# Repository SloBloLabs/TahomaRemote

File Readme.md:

# Tahoma Remote

## Overview
This device is an internet independent shutter control using the Tahoma Local API. At the same time, it serves as a proof of concept for integration of STM32F405 MCU with an ESP8266 using UART communication and Espressif AT command set.

Both hard and software are tailored to the requirements of my domestic Somfy roller shutter installation, consisting of 9 roller shutters controlled by a Tahoma Switch. The layout of buttons reflect the location of roller shutters looking top down to the flat for easy orientation. Adding/removing shutters to the setup is possible, but may require adaption of both hard and software.

This repository contains all ressources to build the device:
 * the firmware for the STM32 MCU
 * a script to upload ESP AT firmware to the ESP MCU
 * the board's KiCad design
 * a 3D model housing the board

## Operation
 * Switch the device on
 * During the startup sequence, Tahoma Remote
   * initializes communication to ESP
   * sets up WIFI connection
   * fetches current shutter states from Tahoma Switch
 * The button colours reflect the actual shutter closures of each motor in HSV colour space:
   * green = up
   * blue = 50%
   * red = closed
   * and any colour inbetween
 * Choose your target closure amount using the slider pot
 * Hit the buttons of corresponding shutters to execute the target closure command
 * While motors are moving, corresponding buttons are blinking
 * Motor status is updated each 1,5 seconds

## Highlights
As a proof of concept, these are the feature highlights of the project:
 * DMA driven UART communication between STM32F405 and ESP8266
 * Client side implementation of AT command set
 * Using Tahoma Local API. No internet required!
 * JSON stream parsing for memory efficient payload consumption (big up for the great [lwjson](https://github.com/MaJerle/lwjson.git) project!)
 * Highly capable RGB Led driver implementation using DMA, I2C and PCA9685PW driver chips
 * FreeRTOS for independent UI and communication threads
 * All firmware code written in plain C/C++ using STM32 LL (Low Level) API
 * Compact design
 * Battery powered

## Installation Notes
### Flashing ESP Firmware
 1. Install esptool using

        brew install esptool
 2. Go to https://github.com/espressif/esp-at/releases and find the link for the latest ESP8266 compatible AT firmware, such as

    [ESP-WROOM-02-AT-V2.3.0.0.zip](https://dl.espressif.com/esp-at/firmwares/esp8266/ESP-WROOM-02-AT-V2.3.0.0.zip)
 3. Download and extract the file into ESP subfolder.<br>
    Within the "factory" subfolder, the archive will contain the firmware binary file called "factory/factory_WROOM-02.bin"

 4. Connect a USB serial adapter such as FTDI Friend or Arduino Uno

        USB Serial Adapter            Tahoma Remote
                       GND ---------> GND
                        TX ---------> EDTX
                        RX ---------> EDRX

 5. Press and hold the ESP Boot button on Tahoma Remote and switch the device on. Then release the button again.
 6. Go to ESP subfolder and issue uploadATFW.sh script (check and apply correct settings regarding PORT and FWPATH variable!)

        ./uploadATFW.sh

    If the command is not executable, add respective rights to it:

        chmod u+x uploadATFW.sh
    
    The expected output looks something like this:

        esptool v5.1.0
        Connected to ESP8266 on /dev/cu.usbserial-XXX:
        Chip type:          ESP8266EX
        Features:           Wi-Fi, 160MHz
        Crystal frequency:  26MHz
        MAC:                e0:98:06:0a:71:a6
        
        Stub flasher running.
        
        Configuring flash size...
        Flash will be erased from 0x00000000 to 0x001fffff...
        Flash parameters set to 0x0241.
        Wrote 2097152 bytes (582385 compressed) at 0x00000000 in 54.0 seconds (310.8 kbit/s).
        Hash of data verified.
        
        Hard resetting via RTS pin...
    
### Flashing STM32 firmware
 1. Install VS Code
 2. Install STM32Cube Extensions for VS Code
 3. Add lwjson as submodule to the project

        git submodule add https://github.com/MaJerle/lwjson.git
        git submodule update --init
 4. Rename config_example.h to config.h and configure your local credentials and system information:
   * WIFI_SSID: your WIFI SSID
   * WIFI_PASSWD: your WIFI password
   * TAHOMA_HOST: the Tahoma Switch hostname, typically in the form 'gateway-\<box pin code\>.local'
   * TAHOMA_AUTH: the developer token generated within Somfy App
   * shutterConfigTable takes a set of roller shutters in the system (see TahomaManger.h for the structure of ShutterConfig entries)
 5. Configure and build the project using device STM32F405RGT6 and GCC toolchain in VSCode
    
    alternatively, if cmake and ninja are installed on the system, you can run these commands:

        cmake --preset Release
        cmake --build --preset Release
 6. Connect ST-Link to the SWO interface on Tahoma Remote
 7. Flash the firmware: Run and Debug and apply "STM32Cube: STLink GDB Server"

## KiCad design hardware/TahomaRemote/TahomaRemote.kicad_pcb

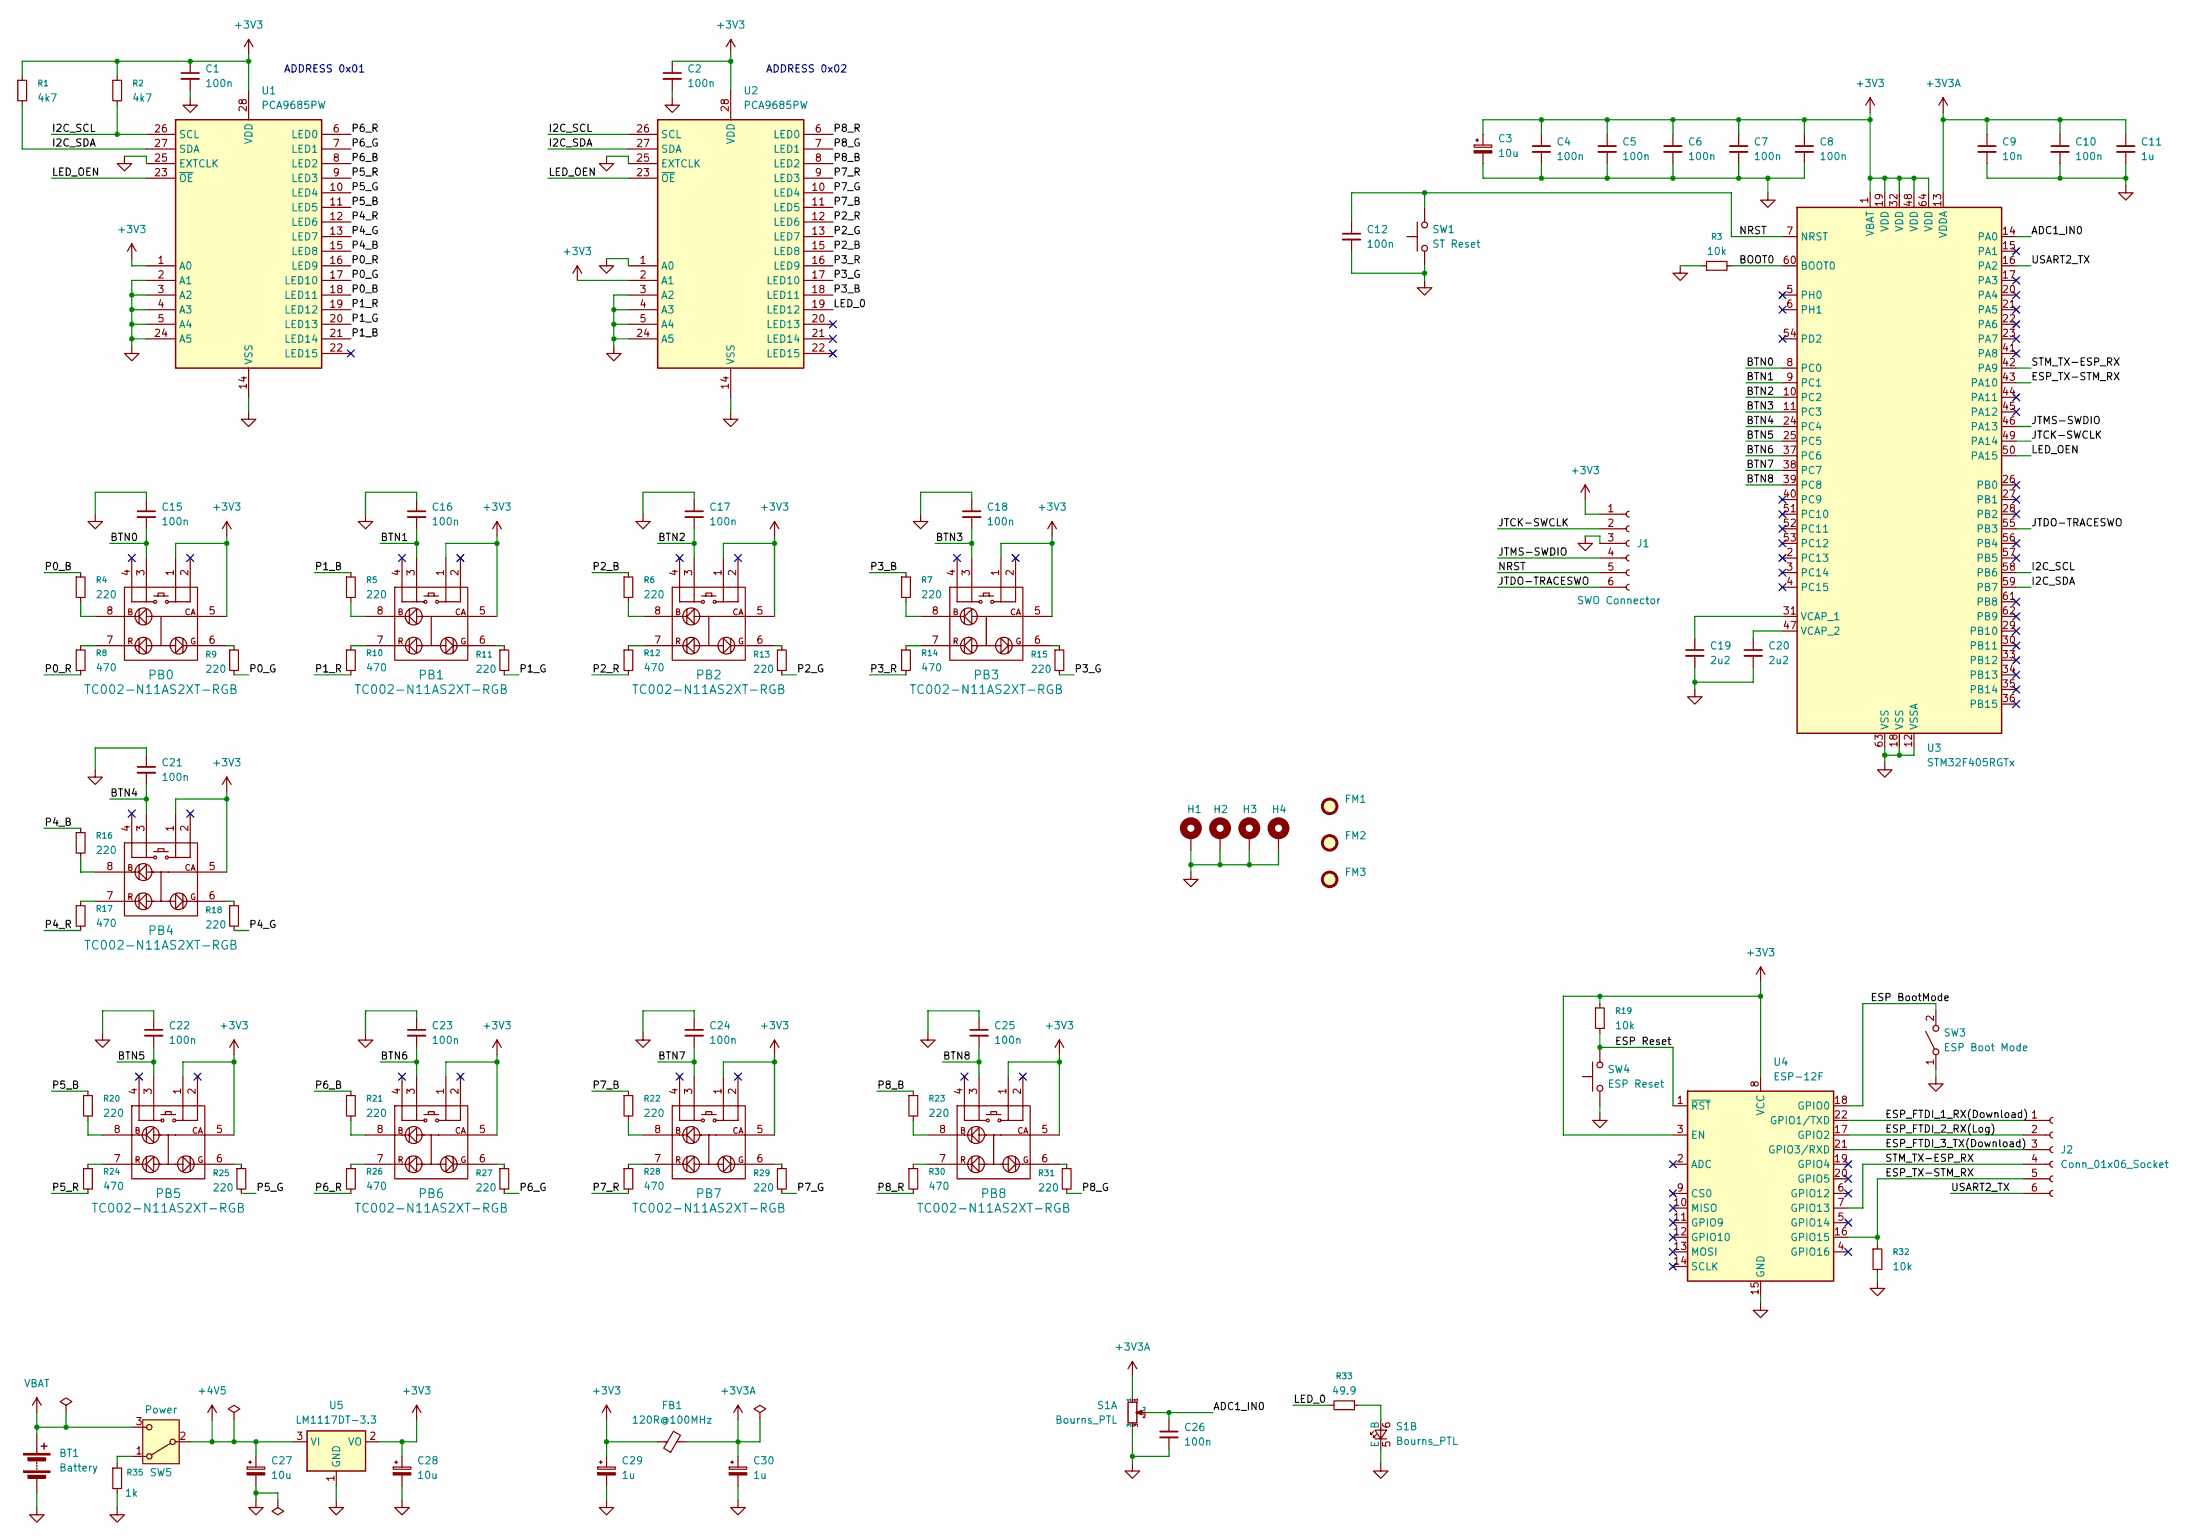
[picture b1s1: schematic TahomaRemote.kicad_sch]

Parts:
BT1: Battery; PinHeader_1x02_P2.54mm_Vertical
C1, C2, C4, C5, C6, C7, C8, C10, C12, C15, C16, C17, C18, C21, C22, C23, C24, C25, C26: 100n; C_0402_1005Metric; LCSC C1525
C3, C27, C28: 10u; CP_EIA-3216-18_Kemet-A; LCSC C7171
C9: 10n; C_0402_1005Metric; LCSC C15195
C11, C29, C30: 1u; C_0402_1005Metric; LCSC C52923
C19, C20: 2u2; C_0402_1005Metric; LCSC C12530
FB1: 120R@100MHz; L_0603_1608Metric
FM1, FM2, FM3: Fiducial; Fiducial_1mm_Mask2mm
H1, H2, H3, H4: MountingHole_Pad; MountingHole_3.2mm_M3_Pad_Via
J1: SWO Connector; PinSocket_1x06_P2.54mm_Vertical
J2: Conn_01x06_Socket; PinSocket_1x06_P2.54mm_Vertical
PB0, PB1, PB2, PB3, PB4, PB5, PB6, PB7, PB8: TC002-N11AS2XT-RGB
R1, R2: 4k7; R_0402_1005Metric; LCSC C25900
R3, R19, R32: 10k; R_0402_1005Metric; LCSC C25744
R4, R5, R6, R7, R9, R11, R13, R15, R16, R18, R20, R21, R22, R23, R25, R27, R29, R31: 220; R_0402_1005Metric; LCSC C25091
R8, R10, R12, R14, R17, R24, R26, R28, R30: 470; R_0402_1005Metric; LCSC C25117
R33: 49.9; R_0402_1005Metric; LCSC C25120
R35: 1k; R_0402_1005Metric; LCSC C11702
S1: Bourns_PTL; Bourns_PTL20
SW1: ST Reset; SW_Push_1P1T_NO_CK_KMR2
SW3: ESP Boot Mode; SW_Push_1P1T_NO_CK_KMR2
SW4: ESP Reset; SW_Push_1P1T_NO_CK_KMR2
SW5: Power; SW_Toggle_MS500
U1, U2: PCA9685PW; TSSOP-28_4.4x9.7mm_P0.65mm
U3: STM32F405RGTx; LQFP-64_10x10mm_P0.5mm
U4: ESP-12F; ESP-12E
U5: LM1117DT-3.3; TO-252-3_TabPin2

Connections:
+3V3: C1.1, C2.1, C3.1, C4.1, C5.1, C6.1, C7.1, C8.1, C28.1, C29.1, FB1.1, J1.1, PB0.1 (UP-A), PB0.5 (CA), PB1.1 (UP-A), PB1.5 (CA), PB2.1 (UP-A), PB2.5 (CA), PB3.1 (UP-A), PB3.5 (CA), PB4.1 (UP-A), PB4.5 (CA), PB5.1 (UP-A), PB5.5 (CA), PB6.1 (UP-A), PB6.5 (CA), PB7.1 (UP-A), PB7.5 (CA), PB8.1 (UP-A), PB8.5 (CA), R1.1, R2.1, R19.1, U1.1 (A0), U1.28 (VDD), U2.2 (A1), U2.28 (VDD), U3.1 (VBAT), U3.19 (VDD), U3.32 (VDD), U3.48 (VDD), U3.64 (VDD), U4.3 (EN), U4.8 (VCC), U5.2 (VO)
+3V3A: C9.1, C10.1, C11.1, C30.1, FB1.2, S1.1, U3.13 (VDDA)
+4V5: C27.1, SW5.2 (B), U5.3 (VI)
/ADC1_IN0: C26.1, S1.2, U3.14 (PA0)
/BOOT0: R3.2, U3.60 (BOOT0)
/BTN0: C15.2, PB0.3 (DOWN-A), U3.8 (PC0)
/BTN1: C16.2, PB1.3 (DOWN-A), U3.9 (PC1)
/BTN2: C17.2, PB2.3 (DOWN-A), U3.10 (PC2)
/BTN3: C18.2, PB3.3 (DOWN-A), U3.11 (PC3)
/BTN4: C21.2, PB4.3 (DOWN-A), U3.24 (PC4)
/BTN5: C22.2, PB5.3 (DOWN-A), U3.25 (PC5)
/BTN6: C23.2, PB6.3 (DOWN-A), U3.37 (PC6)
/BTN7: C24.2, PB7.3 (DOWN-A), U3.38 (PC7)
/BTN8: C25.2, PB8.3 (DOWN-A), U3.39 (PC8)
/ESP BootMode: SW3.2 (B), U4.18 (GPIO0)
/ESP Reset: R19.2, SW4.2, U4.1 (~RST)
/ESP_FTDI_1_RX(Download): J2.1, U4.22 (GPIO1/TXD)
/ESP_FTDI_2_RX(Log): J2.2, U4.17 (GPIO2)
/ESP_FTDI_3_TX(Download): J2.3, U4.21 (GPIO3/RXD)
/ESP_TX-STM_RX: J2.5, R32.1, U3.43 (PA10), U4.16 (GPIO15)
/I2C_SCL: R2.2, U1.26 (SCL), U2.26 (SCL), U3.58 (PB6)
/I2C_SDA: R1.2, U1.27 (SDA), U2.27 (SDA), U3.59 (PB7)
/JTCK-SWCLK: J1.2, U3.49 (PA14)
/JTDO-TRACESWO: J1.6, U3.55 (PB3)
/JTMS-SWDIO: J1.4, U3.46 (PA13)
/LED_0: R33.2, U2.19 (LED12)
/LED_OEN: U1.23 (~OE), U2.23 (~OE), U3.50 (PA15)
/NRST: C12.1, J1.5, SW1.2, U3.7 (NRST)
/P0_B: R4.1, U1.18 (LED11)
/P0_G: R9.2, U1.17 (LED10)
/P0_R: R8.2, U1.16 (LED9)
/P1_B: R5.1, U1.21 (LED14)
/P1_G: R11.2, U1.20 (LED13)
/P1_R: R10.2, U1.19 (LED12)
/P2_B: R6.1, U2.15 (LED8)
/P2_G: R13.2, U2.13 (LED7)
/P2_R: R12.2, U2.12 (LED6)
/P3_B: R7.1, U2.18 (LED11)
/P3_G: R15.2, U2.17 (LED10)
/P3_R: R14.2, U2.16 (LED9)
/P4_B: R16.1, U1.15 (LED8)
/P4_G: R18.2, U1.13 (LED7)
/P4_R: R17.2, U1.12 (LED6)
/P5_B: R20.1, U1.11 (LED5)
/P5_G: R25.2, U1.10 (LED4)
/P5_R: R24.2, U1.9 (LED3)
/P6_B: R21.1, U1.8 (LED2)
/P6_G: R27.2, U1.7 (LED1)
/P6_R: R26.2, U1.6 (LED0)
/P7_B: R22.1, U2.11 (LED5)
/P7_G: R29.2, U2.10 (LED4)
/P7_R: R28.2, U2.9 (LED3)
/P8_B: R23.1, U2.8 (LED2)
/P8_G: R31.2, U2.7 (LED1)
/P8_R: R30.2, U2.6 (LED0)
/STM_TX-ESP_RX: J2.4, U3.42 (PA9), U4.7 (GPIO13)
/USART2_TX: J2.6, U3.16 (PA2)
GND: BT1.2 (-), C1.2, C2.2, C3.2, C4.2, C5.2, C6.2, C7.2, C8.2, C9.2, C10.2, C11.2, C12.2, C15.1, C16.1, C17.1, C18.1, C19.2, C20.2, C21.1, C22.1, C23.1, C24.1, C25.1, C26.2, C27.2, C28.2, C29.2, C30.2, H1.1, H2.1, H3.1, H4.1, J1.3, R3.1, R32.2, R35.2, S1.3, S1.5 (E), SW1.1, SW3.1 (A), SW4.1, U1.2 (A1), U1.3 (A2), U1.4 (A3), U1.5 (A4), U1.14 (VSS), U1.24 (A5), U1.25 (EXTCLK), U2.1 (A0), U2.3 (A2), U2.4 (A3), U2.5 (A4), U2.14 (VSS), U2.24 (A5), U2.25 (EXTCLK), U3.12 (VSSA), U3.18 (VSS), U3.63 (VSS), U4.15 (GND), U5.1 (GND)
unnamed: PB0.8 (B), R4.2
unnamed: PB0.6 (G), R9.1
unnamed: PB0.7 (R), R8.1
unnamed: PB1.8 (B), R5.2
unnamed: PB1.6 (G), R11.1
unnamed: PB1.7 (R), R10.1
unnamed: PB2.8 (B), R6.2
unnamed: PB2.6 (G), R13.1
unnamed: PB2.7 (R), R12.1
unnamed: PB3.8 (B), R7.2
unnamed: PB3.6 (G), R15.1
unnamed: PB3.7 (R), R14.1
unnamed: PB4.8 (B), R16.2
unnamed: PB4.6 (G), R18.1
unnamed: PB4.7 (R), R17.1
unnamed: PB5.8 (B), R20.2
unnamed: PB5.6 (G), R25.1
unnamed: PB5.7 (R), R24.1
unnamed: PB6.8 (B), R21.2
unnamed: PB6.6 (G), R27.1
unnamed: PB6.7 (R), R26.1
unnamed: PB7.8 (B), R22.2
unnamed: PB7.6 (G), R29.1
unnamed: PB7.7 (R), R28.1
unnamed: PB8.8 (B), R23.2
unnamed: PB8.6 (G), R31.1
unnamed: PB8.7 (R), R30.1
unnamed: R33.1, S1.6 (B)
unnamed: R35.1, SW5.1 (A)
unnamed: C19.1, U3.31 (VCAP_1)
unnamed: C20.1, U3.47 (VCAP_2)
VBAT: BT1.1 (+), SW5.3 (C)

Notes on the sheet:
ADDRESS 0x01
ADDRESS 0x02

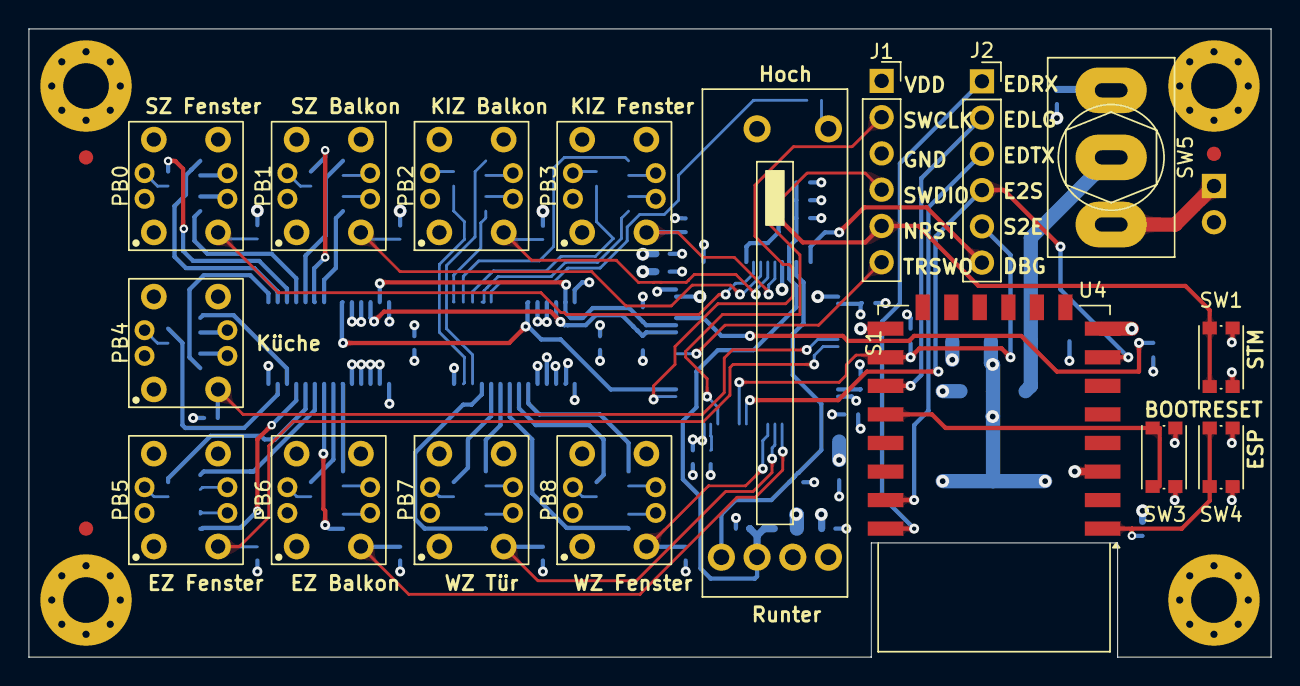
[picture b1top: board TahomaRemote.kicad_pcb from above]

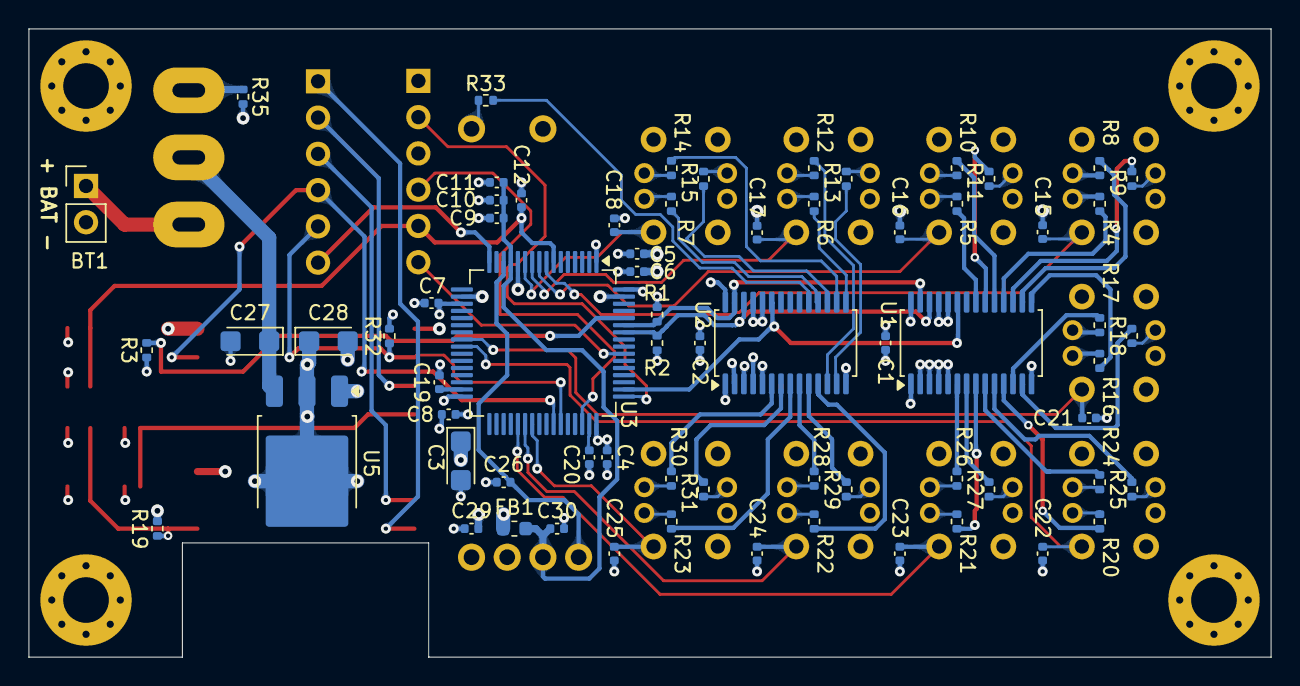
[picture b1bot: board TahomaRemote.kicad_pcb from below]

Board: 4 copper layers, 87.0 x 44.0 mm, 92 parts (68 on the bottom side), 90 nets.

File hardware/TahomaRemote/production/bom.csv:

Designator,Footprint,Quantity,Value,LCSC Part #
BT1,PinHeader_1x02_P2.54mm_Vertical,1,Battery,
"C1, C10, C12, C15, C16, C17, C18, C2, C21, C22, C23, C24, C25, C26, C4, C5, C6, C7, C8",0402,19,100n,C1525
"C11, C29, C30",0402,3,1u,C52923
"C19, C20",0402,2,2u2,C12530
"C27, C28, C3",CP_EIA-3216-18_Kemet-A,3,10u,C7171
C9,0402,1,10n,C15195
FB1,0603,1,120R@100MHz,
J1,PinSocket_1x06_P2.54mm_Vertical,1,SWO Connector,
J2,PinSocket_1x06_P2.54mm_Vertical,1,Conn_01x06_Socket,
"PB0, PB1, PB2, PB3, PB4, PB5, PB6, PB7, PB8",TC002-N11AS2XT-RGB,9,TC002-N11AS2XT-RGB,
"R1, R2",0402,2,4k7,C25900
"R10, R12, R14, R17, R24, R26, R28, R30, R8",0402,9,470,C25117
"R11, R13, R15, R16, R18, R20, R21, R22, R23, R25, R27, R29, R31, R4, R5, R6, R7, R9",0402,18,220,C25091
"R19, R3, R32",0402,3,10k,C25744
R33,0402,1,49.9,C25120
R35,0402,1,1k,C11702
S1,Bourns_PTL20,1,Bourns_PTL,
SW1,SW_Push_1P1T_NO_CK_KMR2,1,ST Reset,
SW3,SW_Push_1P1T_NO_CK_KMR2,1,ESP Boot Mode,
SW4,SW_Push_1P1T_NO_CK_KMR2,1,ESP Reset,
SW5,SW_Toggle_MS500,1,Power,
"U1, U2",TSSOP-28_4.4x9.7mm_P0.65mm,2,PCA9685PW,
U3,LQFP-64_10x10mm_P0.5mm,1,STM32F405RGTx,
U4,ESP-12E,1,ESP-12F,
U5,TO-252-3_TabPin2,1,LM1117DT-3.3,

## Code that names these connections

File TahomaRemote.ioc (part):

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Mcu.Name=STM32F405RGTx
Mcu.Package=LQFP64
Mcu.UserName=STM32F405RGTx
PA0-WKUP.Signal=ADCx_IN0
PA10.Mode=Asynchronous
PA10.Signal=USART1_RX
PA13.Mode=Trace_Asynchronous_SW
PA13.Signal=SYS_JTMS-SWDIO
PA14.Mode=Trace_Asynchronous_SW
PA14.Signal=SYS_JTCK-SWCLK
PA15.GPIOParameters=GPIO_Label
PA15.GPIO_Label=LED_OEN
PA15.Signal=GPIO_Output
PA2.GPIOParameters=GPIO_ModeDefaultOD
PA2.GPIO_ModeDefaultOD=GPIO_MODE_AF_PP
PA2.Mode=Half_duplex(single_wire_mode)
PA2.Signal=USART2_TX
PA3.GPIOParameters=GPIO_Label
PA3.GPIO_Label=LED
PA3.Signal=GPIO_Output
PA9.GPIOParameters=GPIO_PuPd
PA9.GPIO_PuPd=GPIO_NOPULL
PA9.Mode=Asynchronous
PA9.Signal=USART1_TX
PB3.Mode=Trace_Asynchronous_SW
PB3.Signal=SYS_JTDO-SWO
PB6.Mode=I2C
PB6.Signal=I2C1_SCL
PB7.Mode=I2C
PB7.Signal=I2C1_SDA
PC0.GPIOParameters=GPIO_PuPd,GPIO_Label,GPIO_ModeDefaultEXTI
PC0.GPIO_Label=BTN0
PC0.GPIO_ModeDefaultEXTI=GPIO_MODE_IT_FALLING
PC0.GPIO_PuPd=GPIO_PULLDOWN
PC0.Signal=GPXTI0
PC1.GPIOParameters=GPIO_PuPd,GPIO_Label,GPIO_ModeDefaultEXTI
PC1.GPIO_Label=BTN1
PC1.GPIO_ModeDefaultEXTI=GPIO_MODE_IT_FALLING
PC1.GPIO_PuPd=GPIO_PULLDOWN
PC1.Signal=GPXTI1
PC2.GPIOParameters=GPIO_PuPd,GPIO_Label,GPIO_ModeDefaultEXTI
PC2.GPIO_Label=BTN2
PC2.GPIO_ModeDefaultEXTI=GPIO_MODE_IT_FALLING
PC2.GPIO_PuPd=GPIO_PULLDOWN
PC2.Signal=GPXTI2
PC3.GPIOParameters=GPIO_PuPd,GPIO_Label,GPIO_ModeDefaultEXTI
PC3.GPIO_Label=BTN3
PC3.GPIO_ModeDefaultEXTI=GPIO_MODE_IT_FALLING
PC3.GPIO_PuPd=GPIO_PULLDOWN
PC3.Signal=GPXTI3
PC4.GPIOParameters=GPIO_PuPd,GPIO_Label,GPIO_ModeDefaultEXTI
PC4.GPIO_Label=BTN4
PC4.GPIO_ModeDefaultEXTI=GPIO_MODE_IT_FALLING
PC4.GPIO_PuPd=GPIO_PULLDOWN
PC4.Signal=GPXTI4
PC5.GPIOParameters=GPIO_PuPd,GPIO_Label,GPIO_ModeDefaultEXTI
PC5.GPIO_Label=BTN5
PC5.GPIO_ModeDefaultEXTI=GPIO_MODE_IT_FALLING
PC5.GPIO_PuPd=GPIO_PULLDOWN
PC5.Signal=GPXTI5
PC6.GPIOParameters=GPIO_PuPd,GPIO_Label,GPIO_ModeDefaultEXTI
PC6.GPIO_Label=BTN6
PC6.GPIO_ModeDefaultEXTI=GPIO_MODE_IT_FALLING
PC6.GPIO_PuPd=GPIO_PULLDOWN
PC6.Signal=GPXTI6
PC7.GPIOParameters=GPIO_PuPd,GPIO_Label,GPIO_ModeDefaultEXTI
PC7.GPIO_Label=BTN7
PC7.GPIO_ModeDefaultEXTI=GPIO_MODE_IT_FALLING
PC7.GPIO_PuPd=GPIO_PULLDOWN
PC7.Signal=GPXTI7
PC8.GPIOParameters=GPIO_PuPd,GPIO_Label,GPIO_ModeDefaultEXTI
PC8.GPIO_Label=BTN8
PC8.GPIO_ModeDefaultEXTI=GPIO_MODE_IT_FALLING
PC8.GPIO_PuPd=GPIO_PULLDOWN
PC8.Signal=GPXTI8
PH0-OSC_IN.Mode=HSE-External-Oscillator
PH0-OSC_IN.Signal=RCC_OSC_IN
PH1-OSC_OUT.Mode=HSE-External-Oscillator
PH1-OSC_OUT.Signal=RCC_OSC_OUT
RCC.HSE_VALUE=16000000
RCC.SYSCLKFreq_VALUE=168000000
RCC.SYSCLKSource=RCC_SYSCLKSOURCE_PLLCLK
board=custom

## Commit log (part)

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2026-04-01 initial upload
2026-04-02 Add compile commands to Readme
2026-04-20 Add schematic pdf
2026-04-28 Enable configUSE_NEWLIB_REENTRANT
